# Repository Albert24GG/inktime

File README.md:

# InkTime Smartwatch

## Block Diagram

## Hardware Functionality

### Power Management
The power path starts at the **USB-C connector (5V)**, which feeds the **BQ25180 LiPo Charger**. This IC handles the 250mAh battery and provides a system rail (VSYS). To ensure a stable 3.3V regardless of the battery's state of charge, an **RT6160 Buck-Boost regulator** was used. This is critical because it keeps the MCU and E-paper display running even as the battery voltage drops. Furthermore, **MAX17048 Fuel Gauge** was included to get the battery percentage over I2C.

### Compute & Connectivity
The MCU chosen is **nRF52840**. It manages:
*   **I2C Bus:** Shared by the charger, regulator, fuel gauge, IMU, and haptic driver.
*   **SPI Bus:** Used exclusively for the E-paper display to handle fast screen refreshes.
*   **USB:** For firmware recovery and battery charging.
*   **RF:** A 2.4GHz trace leads to a chip antenna for BLE communication with a smartphone.

### Peripherals
*   **Display:** A 1.54" 200x200 E-paper module. Since these displays can leak power even when "off," we added a PFET-based power gate to completely cut VCC to the display during deep sleep.
*   **IMU:** The **BMA421** accelerometer handles step counting in hardware, waking the MCU only when a step is detected to save power.
*   **Haptics:** A **DRV2605L** driver controls an ERM shaker motor for haptic feedback.

## MCU Pinout Mapping

| Peripheral | Pin(s) | Function | Description |
| :--- | :--- | :--- | :--- |
| **I2C SDA** | P0.06 | Data | Shared bus for sensors and power ICs |
| **I2C SCL** | P0.07 | Clock | Shared bus for sensors and power ICs |
| **SPI SCK** | P0.02 | Clock | Dedicated high-speed SPI for E-Paper |
| **SPI MOSI** | P0.03 | Data Out | Dedicated high-speed SPI for E-Paper |
| **SPI CS** | P0.05 | Chip Sel | Dedicated high-speed SPI for E-Paper |
| **EPD DC** | P0.15 | Data/Cmd | Required for display command logic |
| **EPD RST** | P0.16 | Reset | Hardware reset for display controller |
| **EPD BUSY** | P0.17 | Input | MCU checks this before display updates |
| **EPD GATE** | P1.01 | PFET Ctrl | Cuts display power |
| **USB D+ / D-** | D+ / D- | USB Data | Differential pair for firmware/recovery |
| **VBUS** | VBUS | Detect | Used by MCU to detect USB cable attachment |
| **ANT1** | ANT | RF Out | 50-ohm matched trace to 2.4GHz chip antenna |
| **X1** | XC1 / XC2 | 32MHz | High-speed clock for Radio/System |
| **X2** | P0.00 / P0.01 | 32.768kHz | Low-power clock for RTC and Sleep timing |
| **IMU INT1** | P0.08 | Wake-up | Primary IMU interrupt |
| **IMU INT2** | P1.08 | Gesture | Secondary IMU interrupt for advanced gestures/events |
| **PMIC INT** | P0.11 | Charger | Signals charging status changes |
| **Fuel Alert** | P0.10 | Low Batt | Triggers when battery hits a critical % threshold |
| **Haptic EN** | P0.12 | Enable | Power control for the haptic driver |
| **Button Up** | P0.13 | Input | Navigation (Active Low) |
| **Button Dn** | P1.02 | Input | Navigation (Active Low) |
| **Button Ent** | P0.14 | Input | Enter / Confirm (Active Low) |
| **SWD Bus** | SWDIO/CLK | Debug | Programming via Tag-Connect TC2030 |
| **RESET** | P0.18 | Reset | System reset |
| **SWO** | P1.00 | Debug | SWO test pad |

## Design Log

During the development of the PCB and mechanical integration, several adjustments were made to ensure reliability and manufacturability:

*   **EPD Capacitor Tweak:** Changed **EPD_C5 to 1uF** (previously 100nF) after double-checking the display driver datasheet requirements for the internal charge pump.
*   **Silkscreen Optimization:** Because JLCPCB has a minimum text height of 1mm and our board is very dense, I removed labels for small passives. Only major components, connectors, and test pads have silkscreen labels to avoid a "messy" print.
*   **Bottom Layer Connectors:** The pads for the **Battery** and the **Shaker Motor** were moved to the **Bottom Layer**. Since these components live in the bottom of the case (under the PCB), this makes hand-soldering them much easier during assembly.
*   **Inner Layer Pad Cleanup:** To prevent manufacturing errors (shorts) with via-in-pad routing on the dense MCU footprint, I used the `Remove All Non-Functional Pads` option for the internal layers.
*   **Component Sizing:** While I aimed for 0201/0402 where possible, I used **0603 footprints** for the large inductors and decoupling caps in the DC/DC section to meet the voltage/current ratings.
*   **RF Optimization:** The antenna feedline (RF trace) was designed with a width of **0.1505mm**. This was calculated for a **50-ohm impedance match** based on the 4-layer stackup (Coplanar Waveguide with Ground).
*   **Accessibility:** All test pads were placed near the edges of the PCB so they can be reached easily with probes even when the display is mounted.
*   **GND & Thermal Management:** I applied a copper pour on the Top Layer with **via stitching** to the internal Ground Plane.
*   **Antenna Safety:** The antenna keepout zone follows the datasheet dimensions exactly. I also added **via fencing** around the keepout area to minimize interference with the rest of the components.
*   **Manufacturing Files**: CPL and BOM files are provided in JLCPCB standard format.

## Bill of Materials (BOM)

| Qty | Value | Parts | Device | Package | Description | Product Link | Datasheet Link |
|---|---|---|---|---|---|---|---|
| 17 | 1uF/50V | C15, C29, C30, C31, C32, C37, C38, EPD_C1, EPD_C2, EPD_C5, EPD_C6, EPD_C7, EPD_C8, EPD_C9, EPD_C10, EPD_C11, EPD_C12 | GRM155R61H105KE05D | 0402 | SMD Capacitor | [Link](https://jlcpcb.com/partdetail/1609005-GRM155R61H105KE05D/C1518208) | [Datasheet](https://wmsc.lcsc.com/wmsc/upload/file/pdf/v2/lcsc/2201180430_Murata-Electronics-GRM155R61H105KE05D_C1518208.pdf) |
| 6 | 4.7uF/25V | C6, C14, C20, C21, C43, C2-EP-DR | GRM155C61E475ME15D | 0402 | SMD Capacitor | [Link](https://jlcpcb.com/partdetail/6643118-GRM155C61E475ME15D/C5718966) | [Datasheet](https://wmsc.lcsc.com/wmsc/upload/file/pdf/v2/lcsc/2308111413_Murata-Electronics-GRM155C61E475ME15D_C5718966.pdf) |
| 2 | 10uF/25V | C1-EP-DR, C39 | GRM188R61E106KA73D | 0603 | SMD Capacitor | [Link](https://jlcpcb.com/partdetail/320824-GRM188R61E106KA73D/C344022) | [Datasheet](https://www.lcsc.com/datasheet/C344022.pdf) |
| 1 | 10uF/6.3V | C24 | GRM155R60J106ME44D | 0402 | SMD Capacitor | [Link](https://jlcpcb.com/partdetail/MurataElectronics-GRM155R60J106ME44D/C76991) | [Datasheet](https://wmsc.lcsc.com/wmsc/upload/file/pdf/v2/lcsc/2304140030_Murata-Electronics-GRM155R60J106ME44D_C76991.pdf) |
| 2 | 22uF/10V | C25, C33 | GRM188R61A226ME15D | 0603 | SMD Capacitor | [Link](https://jlcpcb.com/partdetail/MurataElectronics-GRM188R61A226ME15D/C84419) | [Datasheet](https://wmsc.lcsc.com/wmsc/upload/file/pdf/v2/lcsc/1810311140_Murata-Electronics-GRM188R61A226ME15D_C84419.pdf) |
| 9 | 100nF/25V | C5, C7, C8, C12, C19, C23, C27, C34, C42 | GRM033R61E104KE14D | 0201 | SMD Capacitor | [Link](https://jlcpcb.com/partdetail/MurataElectronics-GRM033R61E104KE14D/C76939) | [Datasheet](https://wmsc.lcsc.com/wmsc/upload/file/pdf/v2/lcsc/1811081532_Murata-Electronics-GRM033R61E104KE14D_C76939.pdf) |
| 1 | 100pF/50V | C11 | GRM0335C1H101JA01D | 0201 | SMD Capacitor | [Link](https://jlcpcb.com/partdetail/MurataElectronics-GRM0335C1H101JA01D/C76922) | [Datasheet](https://wmsc.lcsc.com/wmsc/upload/file/pdf/v2/lcsc/2304140030_Murata-Electronics-GRM0335C1H101JA01D_C76922.pdf) |
| 1 | 47nF/16V | C16 | GRM033R61C473KE84D | 0201 | SMD Capacitor | [Link](https://jlcpcb.com/partdetail/MurataElectronics-GRM033R61C473KE84D/C88917) | [Datasheet](https://wmsc.lcsc.com/wmsc/upload/file/pdf/v2/lcsc/2304140030_Murata-Electronics-GRM033R61C473KE84D_C88917.pdf) |
| 4 | 12pF/50V | C1, C2, C17, C18 | GRM0335C1H120FA01D | 0201 | SMD Capacitor | [Link](https://jlcpcb.com/partdetail/358666-GRM0335C1H120FA01D/C384960) | [Datasheet](https://www.lcsc.com/datasheet/C384960.pdf) |
| 2 | 1pf/50V | C3, C4 | GRM0335C1H1R0WA01D | 0201 | SMD Capacitor | [Link](https://jlcpcb.com/partdetail/172792-GRM0335C1H1R0WA01D/C161411) | [Datasheet](https://www.lcsc.com/datasheet/C161411.pdf) |
| 3 | 0Ω | R2, R3, R4 | RC0201FR-070RL | 0201 | SMD Resistor | [Link](https://jlcpcb.com/partdetail/YAGEO-RC0201FR070RL/C106227) | [Datasheet](https://www.lcsc.com/datasheet/C106227.pdf) |
| 1 | 470mΩ | R1_EP_DR | KDV02DR470ET | 0201 | SMD Resistor | [Link](https://jlcpcb.com/partdetail/Ohmite-KDV02DR470ET/C4327454) | [Datasheet](https://wmsc.lcsc.com/wmsc/upload/file/pdf/v2/lcsc/2404121342_Ohmite-KDV02DR470ET_C4327454.pdf) |
| 1 | 2.2Ω | R_TYPE_SEL | RC0201FR-072R2L | 0201 | SMD Resistor | [Link](https://jlcpcb.com/partdetail/YAGEO-RC0201FR072R2L/C138154) | [Datasheet](https://www.lcsc.com/datasheet/C138154.pdf) |
| 2 | 3.3KΩ | R17, R18 |  RC0201DR-073K3L| 0201 | SMD Resistor | [Link](https://jlcpcb.com/partdetail/YAGEO-RC0201DR073K3L/C851731) | [Datasheet](https://wmsc.lcsc.com/wmsc/upload/file/pdf/v2/lcsc/2206241815_YAGEO-RC0201DR-073K3L_C851731.pdf) |
| 2 |  5.1KΩ | R1_USB, R2_USB | RT0201BRD075K1L | 0201 | SMD Resistor | [Link](https://jlcpcb.com/partdetail/YAGEO-RT0201BRD075K1L/C852257) | [Datasheet](https://wmsc.lcsc.com/wmsc/upload/file/pdf/v2/lcsc/2210190401_YAGEO-RT0201BRD075K1L_C852257.pdf) |
| 6 | 10KΩ | R5, R7, R8, R9, R2_EP_DR, R_PWR_EPD | RE0201BRE0710KL | 0201 | SMD Resistor | [Link](https://jlcpcb.com/partdetail/YAGEO-RE0201BRE0710KL/C1882653) | [Datasheet](https://wmsc.lcsc.com/wmsc/upload/file/pdf/v2/lcsc/2201280400_YAGEO-RE0201BRE0710KL_C1882653.pdf) |
| 1 | 470nH | L7 | FTC252012SR47MBCA | 2520 | SMD Inductor | [Link](https://www.lcsc.com/product-detail/C5832368.html) | [Datasheet](https://www.lcsc.com/datasheet/C5832368.pdf) |
| 1 | 3.9nH | L1 | LQP03TN3N9B02D | 0201 | SMD Inductor | [Link](https://jlcpcb.com/partdetail/MurataElectronics-LQP03TN3N9B02D/C77115) | [Datasheet](https://wmsc.lcsc.com/wmsc/upload/file/pdf/v2/lcsc/2304140030_Murata-Electronics-LQP03TN3N9B02D_C77115.pdf) |
| 1 | 10uH | L2 | MLF1608E100JT000 | 0603 | SMD Inductor | [Link](https://jlcpcb.com/partdetail/TDK-MLF1608E100JT000/C275361) | [Datasheet](https://wmsc.lcsc.com/wmsc/upload/file/pdf/v2/lcsc/2304140030_TDK-MLF1608E100JT000_C275361.pdf) |
| 1 | 15nH | L3 | LQG15HS15NG02D | 0402 | SMD Inductor | [Link](https://jlcpcb.com/partdetail/MurataElectronics-LQG15HS15NG02D/C576527) | [Datasheet](https://wmsc.lcsc.com/wmsc/upload/file/pdf/v2/lcsc/2308111510_Murata-Electronics-LQG15HS15NG02D_C576527.pdf) |
| 1 | 68uH | L5 | 744043680 | SMD, 4.8x4.8mm | SMD Inductor | [Link](https://jlcpcb.com/partdetail/WurthElektronik-744043680/C2045671) | [Datasheet](https://www.we-online.com/components/products/datasheet/744043680.pdf) |
| 1 | USBLC6-2SC6Y | D3 | USBLC6-2SC6Y | SOT-23-6L | ESD Protection | [Link](https://jlcpcb.com/partdetail/STMicroelectronics-USBLC62SC6Y/C2969755) | [Datasheet](https://wmsc.lcsc.com/wmsc/upload/file/pdf/v2/lcsc/2211080730_STMicroelectronics-USBLC6-2SC6Y_C2969755.pdf) |
| 1 | KH-TYPE-C-16P | J4 | KH-TYPE-C-16P | SMD | USB Type-C Connector | [Link](https://jlcpcb.com/partdetail/Shenzhen_KinghelmElec-KH_TYPE_C16P/C709357) | [Datasheet](https://www.lcsc.com/datasheet/C709357.pdf) |
| 1 | 5034802400 | J1 | 5034802400 | SMD, P=0.5mm | Molex Display Connector | [Link](https://jlcpcb.com/partdetail/MOLEX-5034802400/C122434) | [Datasheet](https://www.molex.com/content/dam/molex/molex-dot-com/products/automated/en-us/salesdrawingpdf/503/503480/5034802400_sd.pdf) |
| 1 | MAX17048G+T10 | U3 | MAX17048G+T10 | DFN-8-EP(2x2) | Fuel Gauge | [Link](https://jlcpcb.com/partdetail/2777647-MAX17048GT10/C2682616) | [Datasheet](https://www.lcsc.com/datasheet/C2682616.pdf) |
| 3 | EVPAKE31A | SW_UP, SW_ENT, SW_DN | EVPAKE31A | SMD,3.9x2.9mm | Push Button | [Link](https://jlcpcb.com/partdetail/PANASONIC-EVPAKE31A/C569760) | [Datasheet](https://wmsc.lcsc.com/wmsc/upload/file/pdf/v2/lcsc/2301111010_PANASONIC-EVPAKE31A_C569760.pdf) |
| 1 | DRV2605YZFR | IC2 | DRV2605YZFR | DSBGA-9 | Haptic Driver | [Link](https://jlcpcb.com/partdetail/TexasInstruments-DRV2605YZFR/C81079) | [Datasheet](https://www.ti.com/cn/lit/ds/symlink/drv2605.pdf?ts=1775581743191&ref_url=https%253A%252F%252Fjlcpcb.com%252F) |
| 1 | DMG2305UX-7 | Q1 | DMG2305UX-7 | SOT-23 | EPD Power Gate | [Link](https://jlcpcb.com/partdetail/DiodesIncorporated-DMG2305UX7/C150470) | [Datasheet](https://www.lcsc.com/datasheet/C150470.pdf) |
| 1 | SI1308EDL-T1-GE3 | Q3 | SI1308EDL-T1-GE3 | SOT-323 | EPD Boost Converter Gate | [Link](https://jlcpcb.com/partdetail/VishayIntertech-SI1308EDL_T1GE3/C469327) | [Datasheet](https://www.lcsc.com/datasheet/C469327.pdf) |
| 3 | MBR0530 | D2, D4, D5 | MBR0530 | SOD-123 | EPD Boost Converter Schottky Diode | [Link](https://jlcpcb.com/partdetail/Yangzhou_Yangjie_ElecTech-MBR0530/C699108) | [Datasheet](https://www.lcsc.com/datasheet/C699108.pdf) |
| 1 | BMA421 | IC3 | BMA421 | LGA-12(2x2) | Accelerometer (IMU) | [Link](https://jlcpcb.com/partdetail/BoschSensortec-BMA421/C5242966) | [Datasheet](https://files.pine64.org/doc/datasheet/pinetime/BST-BMA421-FL000.pdf) |
| 1 | RT6160AWSC | IC9 | RT6160AWSC | WLCSP-15B(2.3x1.4) | DC/DC Converter | [Link](https://jlcpcb.com/partdetail/RichtekTech-RT6160AWSC/C7065276) | [Datasheet](https://wmsc.lcsc.com/wmsc/upload/file/pdf/v2/lcsc/2312271436_Richtek-Tech-RT6160AWSC_C7065276.pdf) |
| 1 | BQ25180YBGR | IC1 | BQ25180YBGR | DSBGA-8(1.1x1.6) | LiPo Charger | [Link](https://jlcpcb.com/partdetail/TexasInstruments-BQ25180YBGR/C3682423) | [Datasheet](https://www.ti.com/cn/lit/ds/symlink/bq25180.pdf?ts=1775521983580) |
| 1 | 2450AT18B100E | ANT1 | 2450AT18B100E | 1206 | RF Antenna | [Link](https://jlcpcb.com/partdetail/JohansonDielectrics-2450AT18B100E/C2917717) | [Datasheet](https://www.lcsc.com/datasheet/C2917717.pdf) |
| 1 | NRF52840-QIAA-R | U1 | NRF52840-QIAA-R | AQFN-73-EP(7x7) | Microcontroller (MCU) | [Link](https://jlcpcb.com/partdetail/NordicSemicon-NRF52840_QIAAR/C190794) | [Datasheet](https://www.lcsc.com/datasheet/C190794.pdf) |
| 1 | X1A0000910005 | X2 | X1A0000910005 | SMD3215-2P | Low Frequency Crystal | [Link](https://jlcpcb.com/partdetail/SeikoEpson-X1A0000910005/C255869) | [Datasheet](https://wmsc.lcsc.com/wmsc/upload/file/pdf/v2/lcsc/2008251105_Seiko-Epson-X1A0000910005_C255869.pdf) |
| 1 | Q22FA12800025 | X1 | Q22FA12800025 | SMD2016-4P | High Frequency Crystal | [Link](https://jlcpcb.com/partdetail/SeikoEpson-Q22FA12800025/C187794) | [Datasheet](https://www.lcsc.com/datasheet/C187794.pdf) |
| 1 | AKYGA LP502030 | - | AKYGA LP502030 | - | 3.7V/250mAh LiPo Battery | [Link](https://www.tme.eu/dk/en/details/aky-lp502030/rechargeable-batteries/akyga-battery/aky0106/) | [Datasheet](https://www.tme.eu/Document/b9e12bf26ad0ba929a22ab5d58f022cd/AKY0106.pdf) |
| 1 | WSH-12561 | - | WSH-12561 | - | 1.54" E-Paper Display, 200x200px | [Link](https://www.tme.eu/ie/en/details/wsh-12561/e-paper/waveshare/12561/) | [Datasheet](https://www.tme.eu/Document/0ca57a8ffbcd57b5bca53252eb9d6ec3/WSH-12561.pdf) |
| 1 | FIT0774 | - | FIT0774 | - | Shaker | [Link](https://www.tme.eu/ro/details/df-fit0774/motoare-dc/dfrobot/fit0774/) | [Datasheet](https://www.mouser.com/pdfDocs/ProductOverview_DFRobot-FIT0774.pdf) |
| 1 | TC2030-IDC | J2 | TC2030-IDC | PCB Footprint | Debug Connector | - | - |

## License
This project is licensed under the **MIT License**. See the `LICENSE` file for details.

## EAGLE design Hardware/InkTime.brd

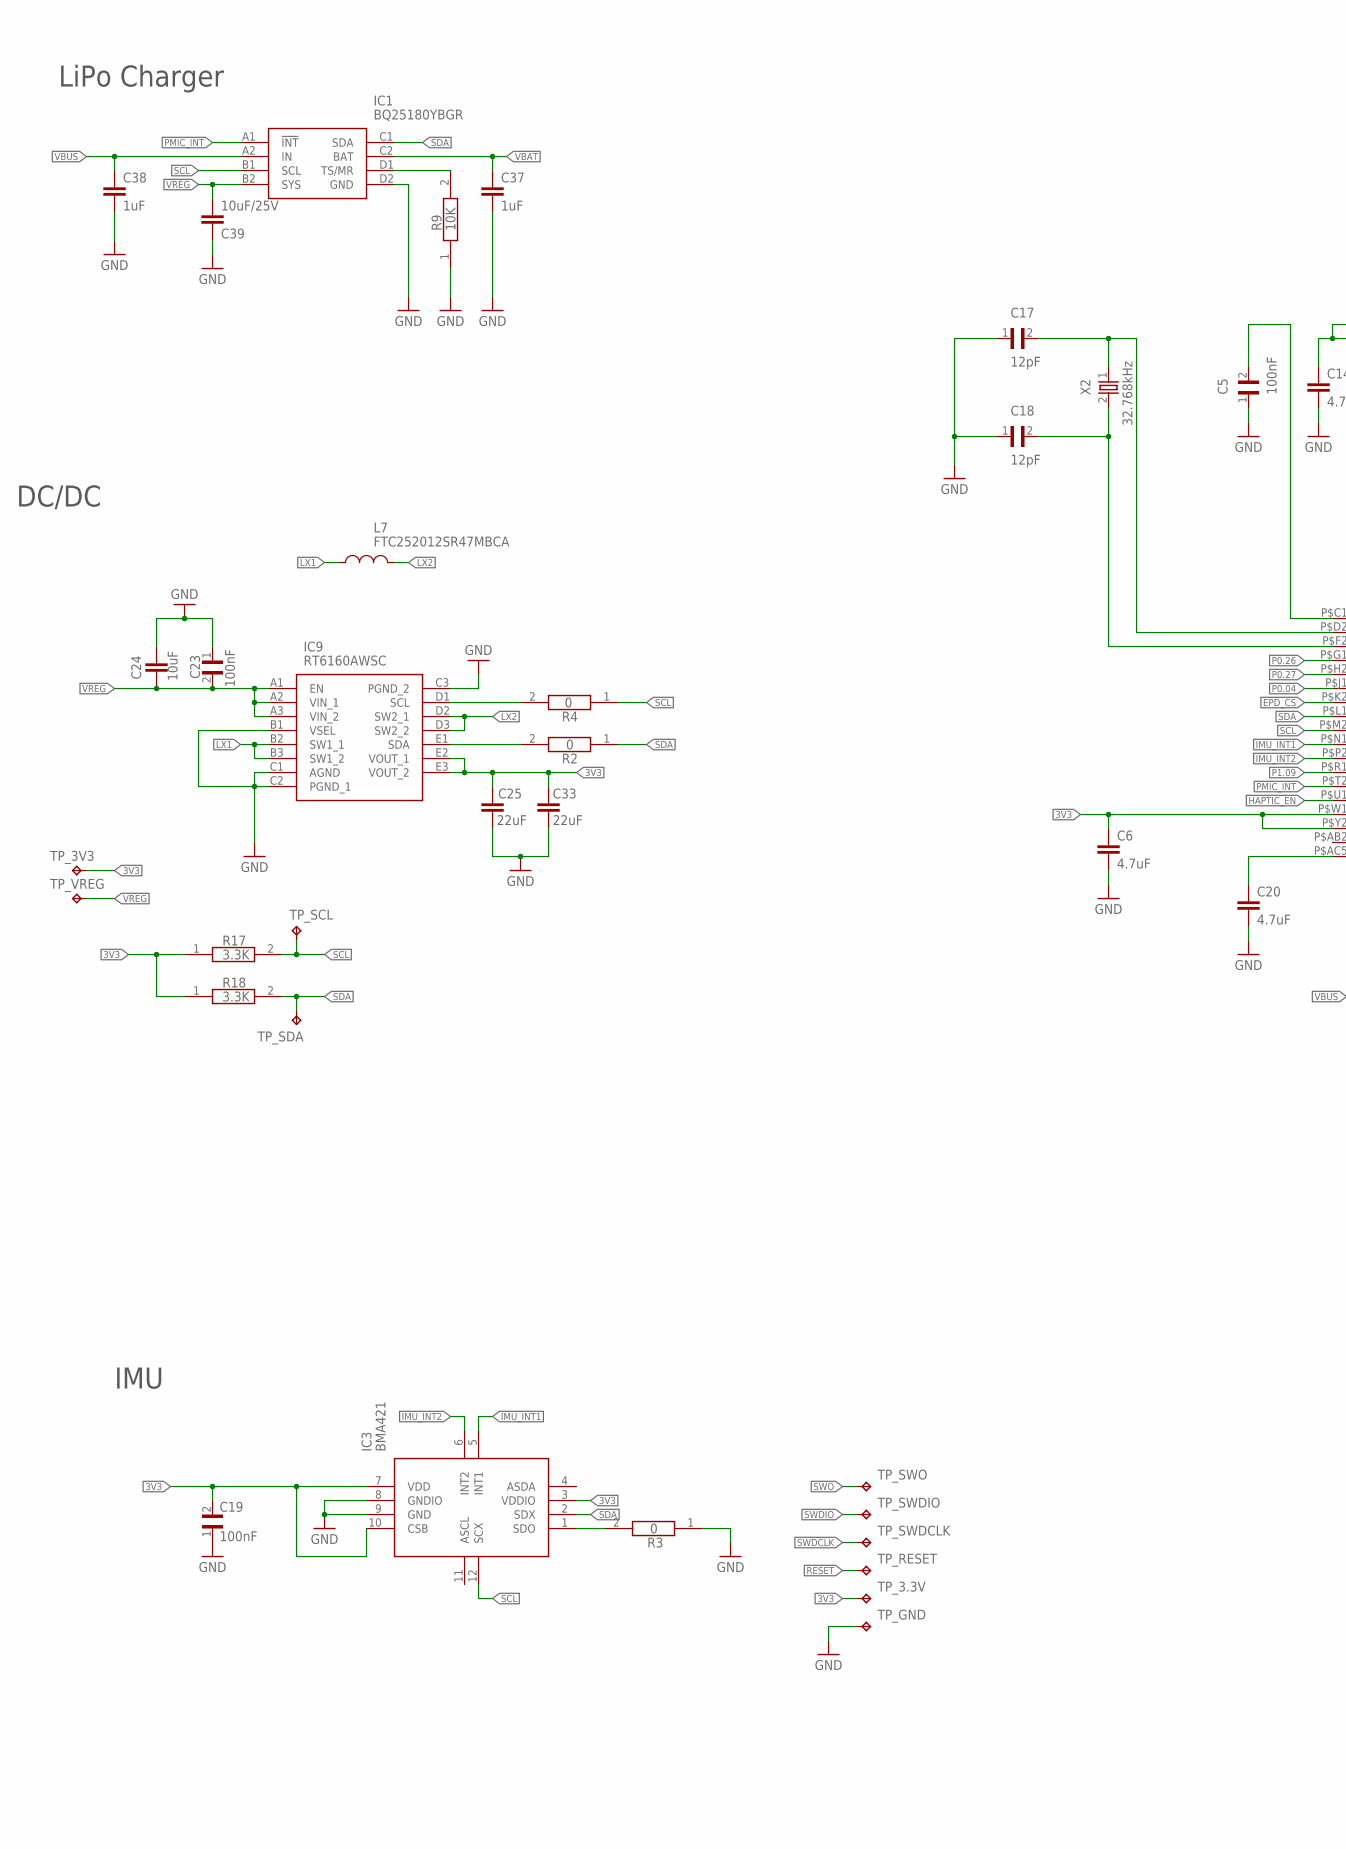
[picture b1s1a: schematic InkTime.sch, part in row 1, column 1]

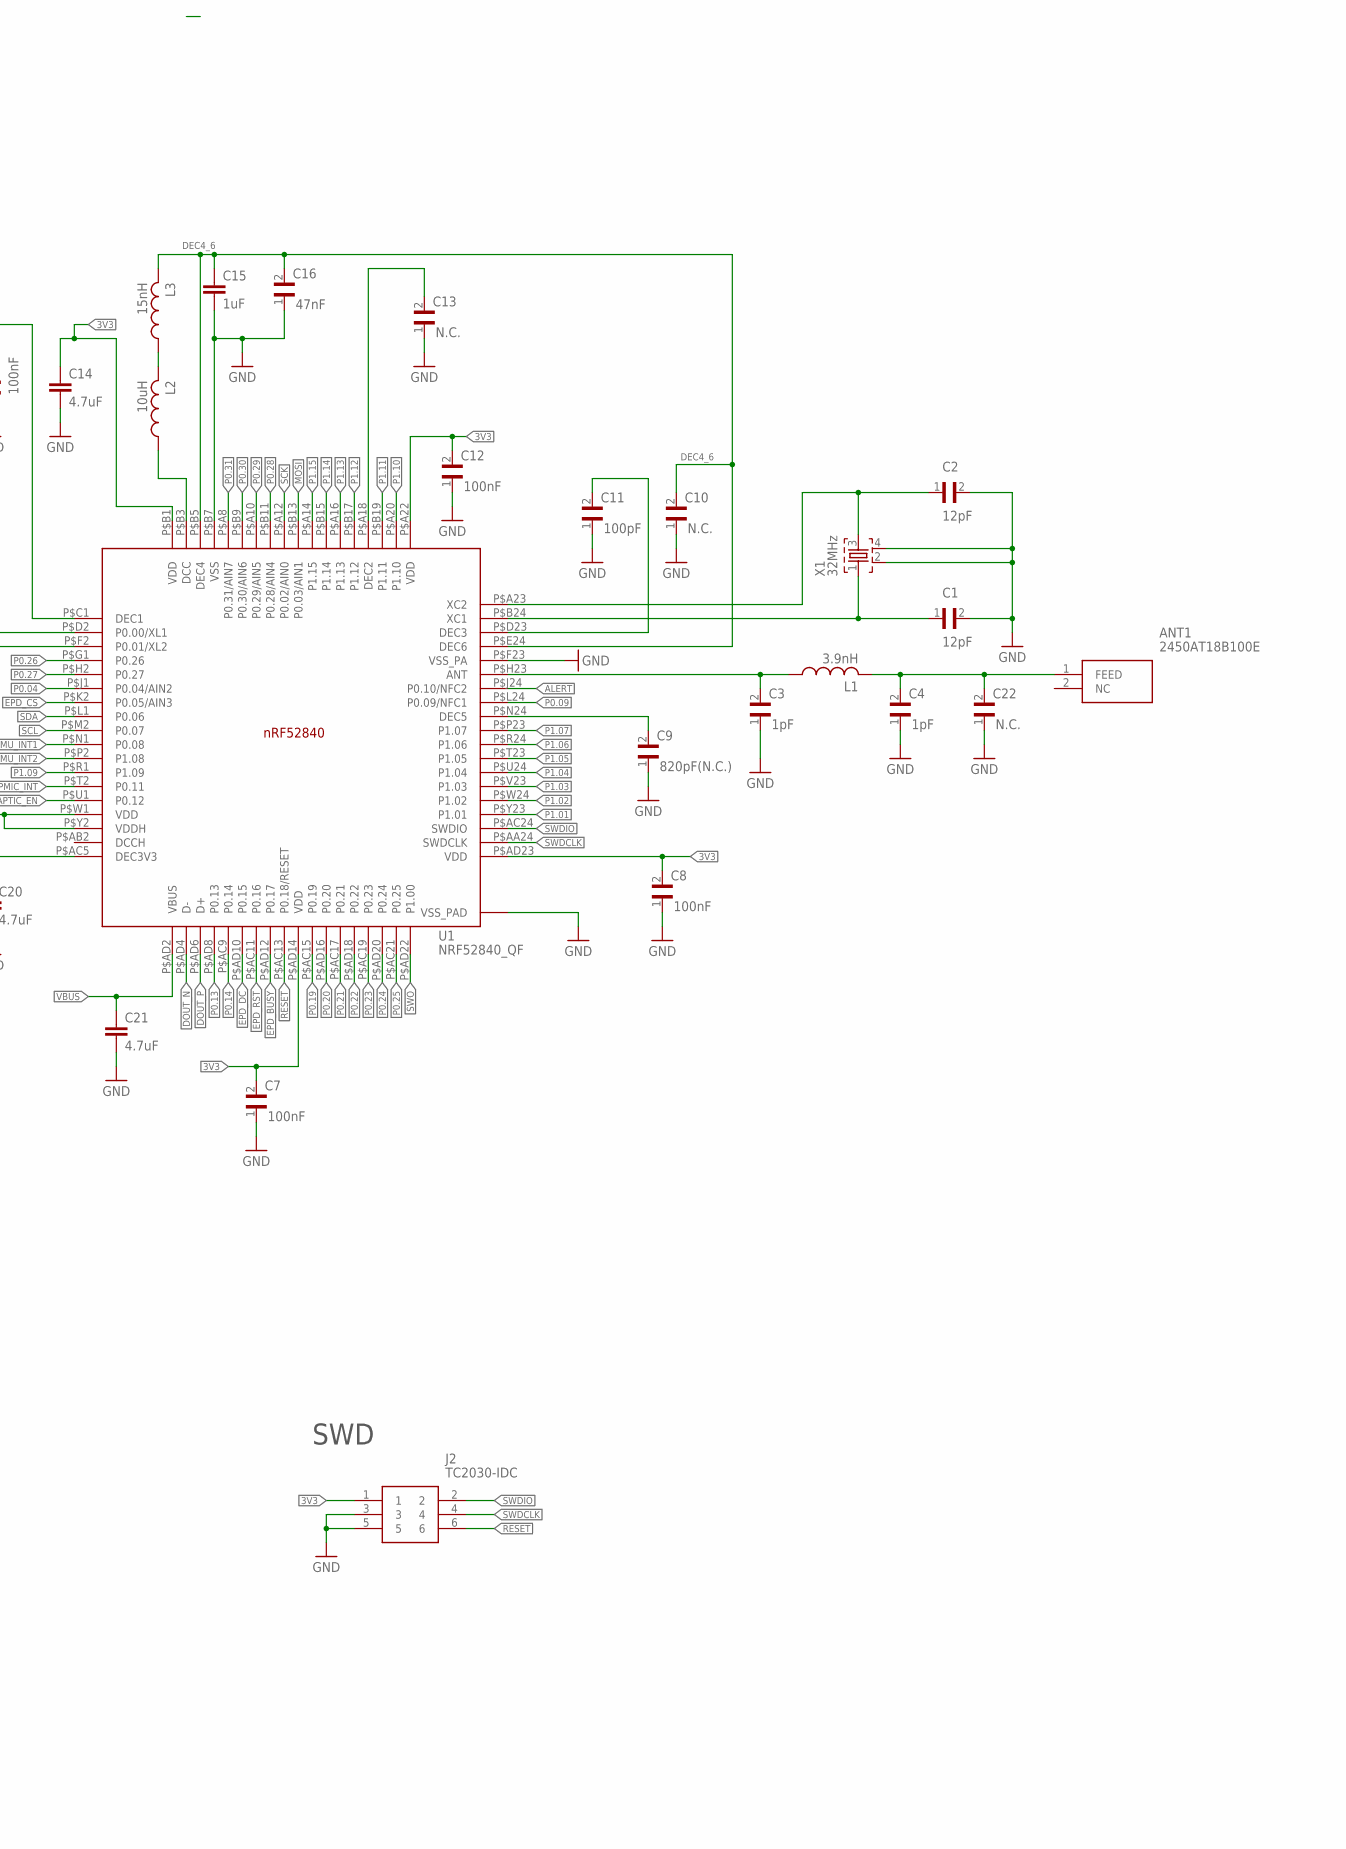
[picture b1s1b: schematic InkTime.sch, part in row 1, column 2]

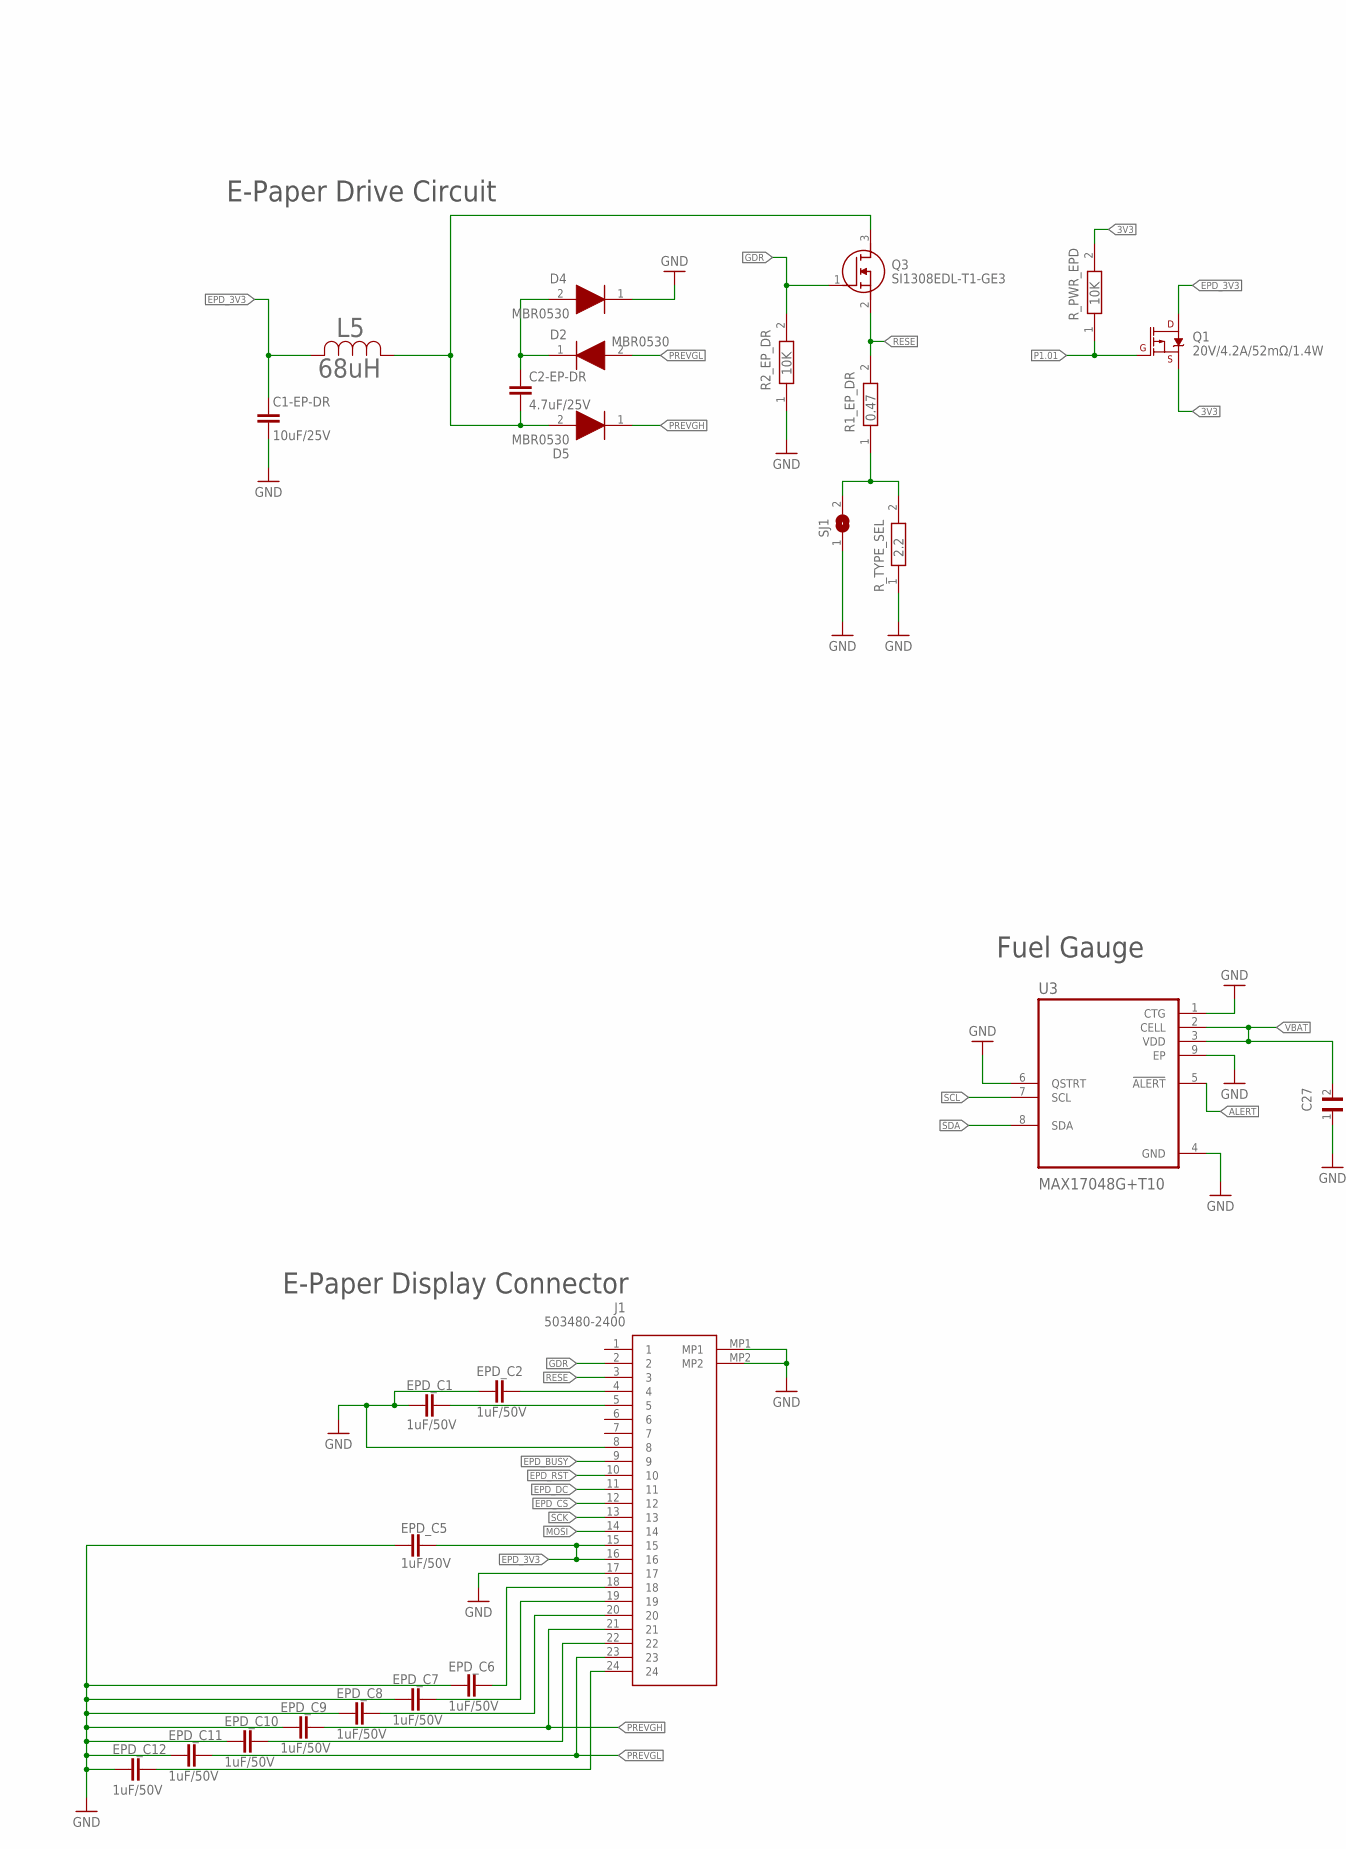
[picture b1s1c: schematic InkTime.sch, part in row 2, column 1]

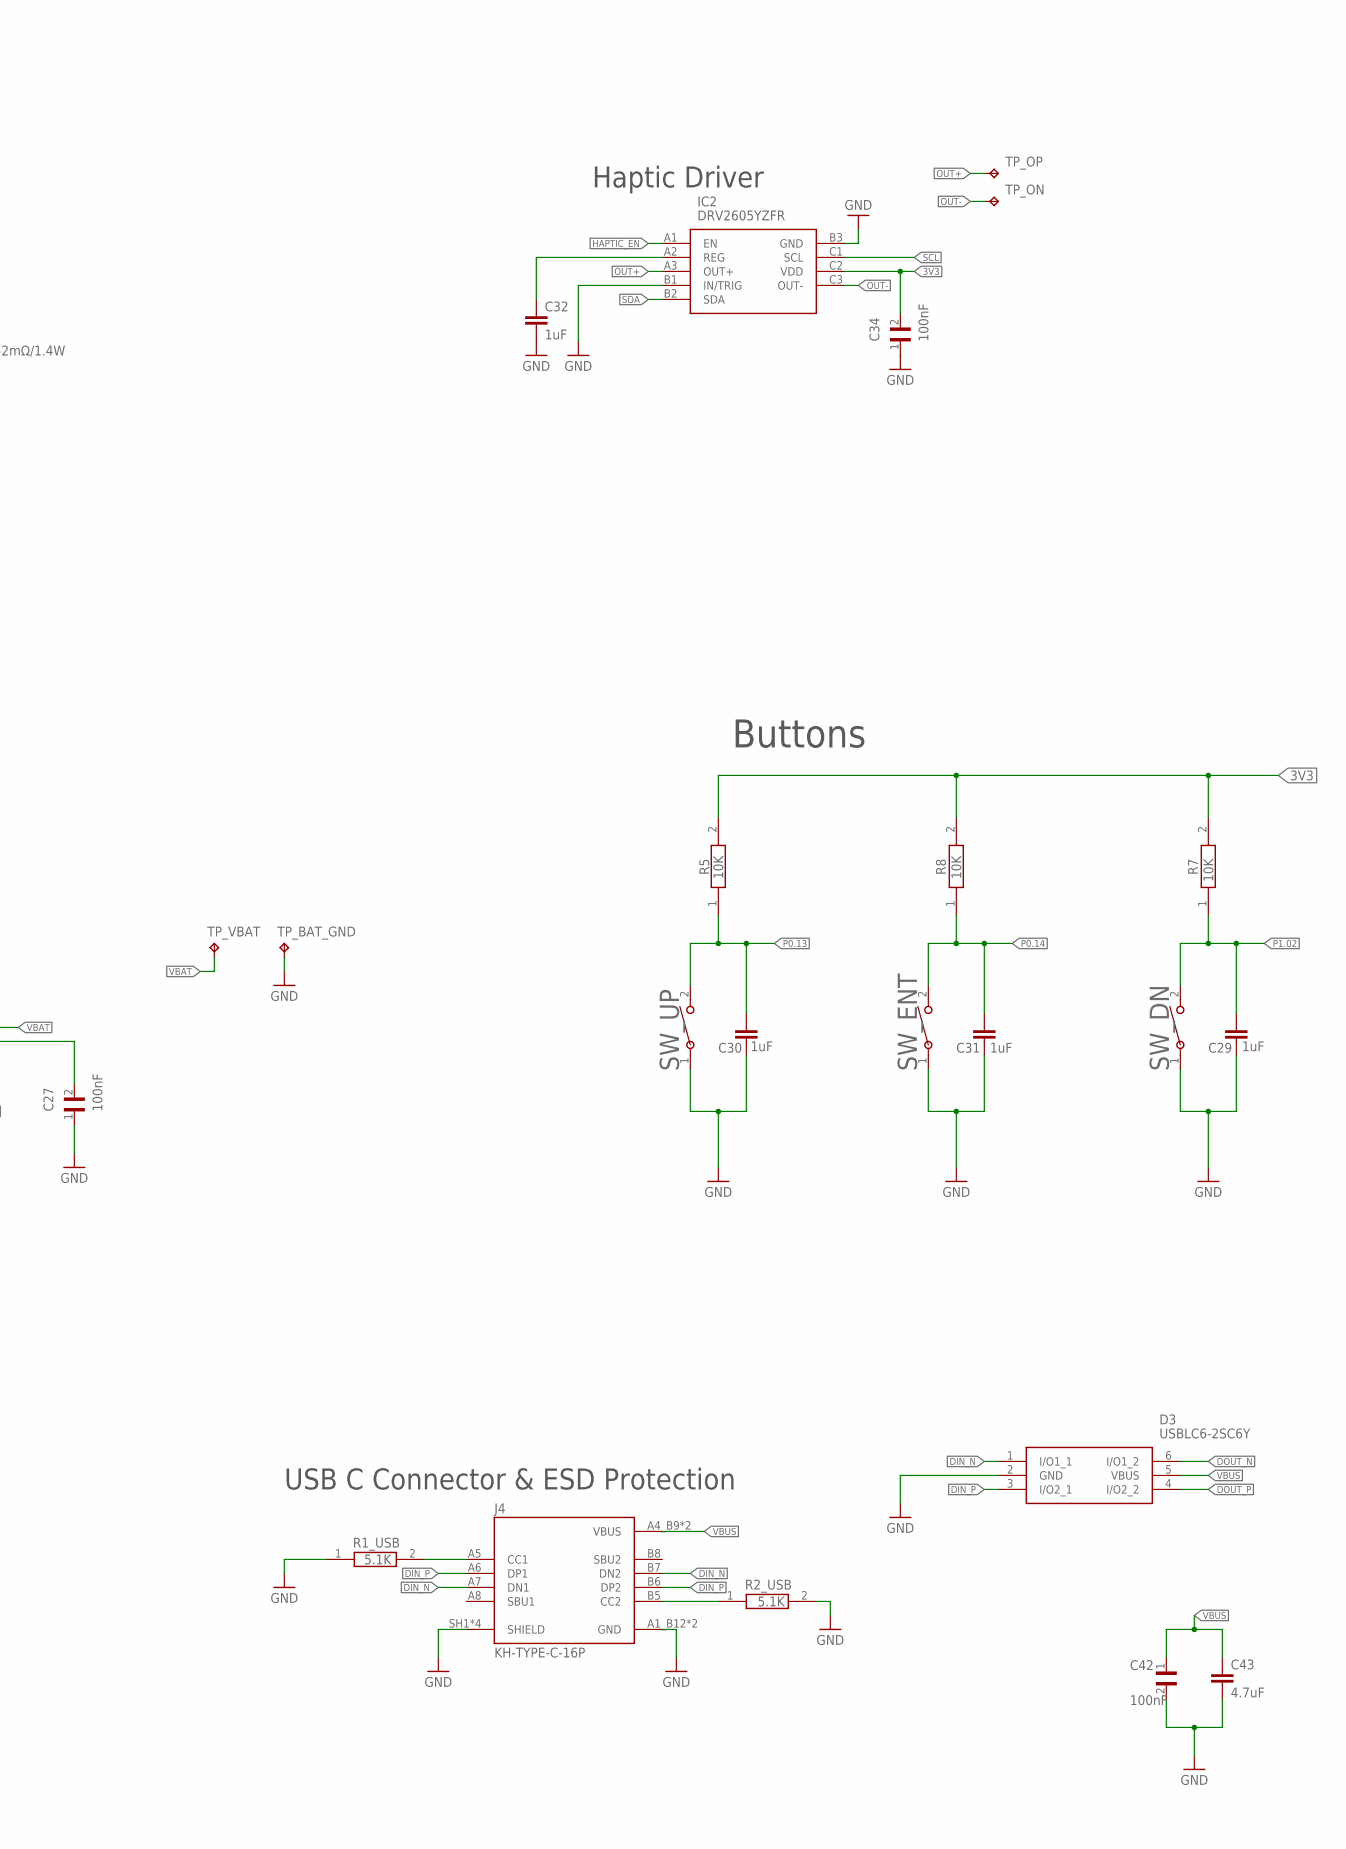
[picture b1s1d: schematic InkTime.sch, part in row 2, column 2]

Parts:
ANT1: 2450AT18B100E; 2450AT18B100E_ANTC3216X140N
C1, C2, C17, C18: 12pF; GRM011R60J152KE01L_2_CAPC0201X13N
C1-EP-DR, C39: 10uF/25V; NORDIC_NRF_3_RESC0603_N
C2-EP-DR: 4.7uF/25V; PERFECT_0402_0402
C3, C4: 1pF; GRM011R60J152KE01L_2_CAPC0201X13N
C5, C7, C8, C12, C19, C23, C27, C34, C42: 100nF; GRM011R60J152KE01L_2_CAPC0201X13N
C6, C14, C20, C21, C43: 4.7uF; PERFECT_0402_0402
C9: 820pF(N.C.); GRM011R60J152KE01L_2_CAPC0201X13N
C10, C13, C22: N.C.; GRM011R60J152KE01L_2_CAPC0201X13N
C11: 100pF; GRM011R60J152KE01L_2_CAPC0201X13N
C15, C29, C30, C31, C32, C37, C38: 1uF; PERFECT_0402_0402
C16: 47nF; GRM011R60J152KE01L_2_CAPC0201X13N
C24: 10uF; PERFECT_0402_0402
C25, C33: 22uF; NORDIC_NRF_3_RESC0603_N
D2, D4, D5: MBR0530; ESP32_C6_LIBRARY_5_SOD3716X135N
D3: USBLC6-2SC6Y; ESP32_C6_LIBRARY_3_SOT95P280X145-6N
EPD_C1, EPD_C2, EPD_C5, EPD_C6, EPD_C7, EPD_C8, EPD_C9, EPD_C10, EPD_C11, EPD_C12: 1uF/50V; PERFECT_0402_0402
IC1: BQ25180YBGR; BQ25180YBGR_BGA8C40P2X4_100X155X50
IC2: DRV2605YZFR; DRV2605YZFR_BGA9C50P3X3_144X144X62
IC3: BMA421; BMA423_BMA423
IC9: RT6160AWSC; RT6160AWSC_BGA15C40P3X5_140X230X60
J1: 503480-2400; 503480-2400_5034802400
J2: TC2030-IDC; TC2030-IDC_TC2030IDC
J4: KH-TYPE-C-16P; KH-TYPE-C-16P_KINGHELM_KH-TYPE-C-16P
L1: 3.9nH; NORDIC_NRF_2_RESC0201_N
L2: 10uH; NORDIC_NRF_2_RESC0603_N
L3: 15nH; NORDIC_NRF_2_RESC0402_N
L5: 68uH; ESP32_C6_LIBRARY_2_IND_4828-WE-TPC_WRE
L7: FTC252012SR47MBCA
Q1: 20V/4.2A/52mΩ/1.4W; ESP32_C6_LIBRARY_4_ESP32_C6_LIBRARY_4_ESP32_C6_LIBRARY_4_ES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
Q3: SI1308EDL-T1-GE3; ESP32_C6_LIBRARY_6_SOT65P210X110-3N
R1_EP_DR: 0.47; ERA-1AEB3401C_0201
R1_USB, R2_USB: 5.1K; ERA-1AEB3401C_0201
R2, R3, R4: 0; ERA-1AEB3401C_0201
R2_EP_DR, R5, R7, R8, R9: 10K; ERA-1AEB3401C_0201
R17, R18: 3.3K; ERA-1AEB3401C_0201
R_PWR_EPD: 10K; ERA-1AEB3401C_0201
R_TYPE_SEL: 2.2; ERA-1AEB3401C_0201
SJ1: ESP32_C6_LIBRARY_7_JUMPER_SJ
SW_DN: 2025-10-22_07-23-44_LIBRARY_EVP-AKE31ASW_EVP-AKE3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; 2025-10-22_07-23-44_LIBRARY_SW_EVP-AKE31A_PAN
SW_ENT: 2025-10-22_07-23-44_LIBRARY_EVP-AKE31ASW_EVP-AKE3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; 2025-10-22_07-23-44_LIBRARY_SW_EVP-AKE31A_PAN
SW_UP: 2025-10-22_07-23-44_LIBRARY_EVP-AKE31ASW_EVP-AKE3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; 2025-10-22_07-23-44_LIBRARY_SW_EVP-AKE31A_PAN
TP_3.3V, TP_3V3: HECTOR_WATCH_1_TPTP20R; HECTOR_WATCH_1_TP20R
TP_BAT_GND: HECTOR_WATCH_1_TPTP20R; HECTOR_WATCH_1_TP20R
TP_GND: HECTOR_WATCH_1_TPTP20R; HECTOR_WATCH_1_TP20R
TP_ON: HECTOR_WATCH_1_TPTP20R; HECTOR_WATCH_1_TP20R
TP_OP: HECTOR_WATCH_1_TPTP20R; HECTOR_WATCH_1_TP20R
TP_RESET: HECTOR_WATCH_1_TPTP20R; HECTOR_WATCH_1_TP20R
TP_SCL: HECTOR_WATCH_1_TPTP20R; HECTOR_WATCH_1_TP20R
TP_SDA: HECTOR_WATCH_1_TPTP20R; HECTOR_WATCH_1_TP20R
TP_SWDCLK: HECTOR_WATCH_1_TPTP20R; HECTOR_WATCH_1_TP20R
TP_SWDIO: HECTOR_WATCH_1_TPTP20R; HECTOR_WATCH_1_TP20R
TP_SWO: HECTOR_WATCH_1_TPTP20R; HECTOR_WATCH_1_TP20R
TP_VBAT: HECTOR_WATCH_1_TPTP20R; HECTOR_WATCH_1_TP20R
TP_VREG: HECTOR_WATCH_1_TPTP20R; HECTOR_WATCH_1_TP20R
U1: NRF52840_QF; NORDIC_NRF_4_AQFN50P700X700X85_HS-74N
U3: MAX17048G+T10; ESP32_C6_LIBRARY_SON50P200X200X80-9N
X1: 32MHz; NORDIC_NRF_BT-XTAL_2016_N
X2: 32.768kHz; NORDIC_NRF_1_XTAL_3215_N

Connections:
3V3: C6.1, C7.2, C8.2, C12.2, C14.1, C19.2, C25.1, C33.1, C34.2, IC2.C2 (VDD), IC3.3 (VDDIO), IC3.7 (VDD), IC3.10 (CSB), IC9.E2 (VOUT_1), IC9.E3 (VOUT_2), J2.1, Q1.2 (S), R5.2, R7.2, R8.2, R17.1, R18.1, R_PWR_EPD.2, TP_3.3V.TP, TP_3V3.TP, U1.P$A22 (VDD), U1.P$AD14 (VDD), U1.P$AD23 (VDD), U1.P$B1 (VDD), U1.P$W1 (VDD), U1.P$Y2 (VDDH)
ALERT: U1.P$J24 (P0.10/NFC2), U3.5 (!ALERT)
DEC4_6: C10.2, C15.1, C16.2, L3.2, U1.P$B5 (DEC4), U1.P$E24 (DEC6)
DIN_N: D3.1 (I/O1_1), J4.A7 (DN1), J4.B7 (DN2)
DIN_P: D3.3 (I/O2_1), J4.A6 (DP1), J4.B6 (DP2)
DOUT_N: D3.6 (I/O1_2), U1.P$AD4 (D-)
DOUT_P: D3.4 (I/O2_2), U1.P$AD6 (D+)
EPD_3V3: C1-EP-DR.1, EPD_C5.2, J1.15, J1.16, L5.2, Q1.3 (D)
EPD_BUSY: J1.9, U1.P$AD12 (P0.17)
EPD_CS: J1.12, U1.P$K2 (P0.05/AIN3)
EPD_DC: J1.11, U1.P$AD10 (P0.15)
EPD_RST: J1.10, U1.P$AC11 (P0.16)
GDR: J1.2, Q3.1 (G), R2_EP_DR.2
GND: C1.2, C1-EP-DR.2, C2.2, C3.1, C4.1, C5.1, C6.2, C7.1, C8.1, C9.1, C10.1, C11.1, C12.1, C13.1, C14.2, C15.2, C16.1, C17.1, C18.1, C19.1, C20.2, C21.2, C22.1, C23.1, C24.1, C25.2, C27.1, C29.1, C30.1, C31.1, C32.2, C33.2, C34.1, C37.2, C38.2, C39.2, C42.2, C43.2, D3.2 (GND), D4.1 (K), EPD_C1.1, EPD_C2.1, EPD_C5.1, EPD_C6.1, EPD_C7.1, EPD_C8.1, EPD_C9.1, EPD_C10.1, EPD_C11.1, EPD_C12.1, IC1.D2 (GND), IC2.B1 (IN/TRIG), IC2.B3 (GND), IC3.8 (GNDIO), IC3.9 (GND), IC9.B1 (VSEL), IC9.C1 (AGND), IC9.C2 (PGND_1), IC9.C3 (PGND_2), J1.8, J1.17, J1.MP1, J1.MP2, J2.3, J2.5, J4.A1_B12 (GND), J4.A12_B1 (GND), J4.SH1 (SHIELD), J4.SH2 (SHIELD), J4.SH3 (SHIELD), J4.SH4 (SHIELD), R1_USB.1, R2_EP_DR.1, R2_USB.2, R3.1, R9.1, R_TYPE_SEL.1, SJ1.1, SW_DN.1, SW_ENT.1, SW_UP.1, TP_BAT_GND.TP, TP_GND.TP, U1.P$74 (VSS_PAD), U1.P$75 (VSS_PAD), U1.P$76 (VSS_PAD), U1.P$77 (VSS_PAD), U1.P$78 (VSS_PAD), U1.P$79 (VSS_PAD), U1.P$80 (VSS_PAD), U1.P$81 (VSS_PAD), U1.P$82 (VSS_PAD), U1.P$83 (VSS_PAD), U1.P$84 (VSS_PAD), U1.P$85 (VSS_PAD), U1.P$86 (VSS_PAD), U1.P$87 (VSS_PAD), U1.P$88 (VSS_PAD), U1.P$89 (VSS_PAD), U1.P$90 (VSS_PAD), U1.P$B7 (VSS), U1.P$F23 (VSS_PA), U3.1 (CTG), U3.4 (GND), U3.6 (QSTRT), U3.9 (EP), X1.2, X1.4
HAPTIC_EN: IC2.A1 (EN), U1.P$U1 (P0.12)
IMU_INT1: IC3.5 (INT1), U1.P$N1 (P0.08)
IMU_INT2: IC3.6 (INT2), U1.P$P2 (P1.08)
LX1: IC9.B2 (SW1_1), IC9.B3 (SW1_2), L7.1
LX2: IC9.D2 (SW2_1), IC9.D3 (SW2_2), L7.2
MOSI: J1.14, U1.P$B13 (P0.03/AIN1)
unnamed: J4.A5 (CC1), R1_USB.2
unnamed: EPD_C12.2, J1.24
unnamed: C17.2, U1.P$D2 (P0.00/XL1), X2.1
unnamed: EPD_C2.2, J1.4
unnamed: C20.1, U1.P$AC5 (DEC3V3)
unnamed: EPD_C1.2, J1.5
unnamed: EPD_C10.2, J1.22
unnamed: J4.B5 (CC2), R2_USB.1
unnamed: C32.1, IC2.A2 (REG)
unnamed: EPD_C8.2, J1.20
unnamed: EPD_C7.2, J1.19
unnamed: EPD_C6.2, J1.18
unnamed: C2-EP-DR.2, D5.2 (A), L5.1, Q3.3 (D)
unnamed: C2-EP-DR.1, D2.1 (K), D4.2 (A)
unnamed: IC9.D1 (SCL), R4.2
unnamed: C18.2, U1.P$F2 (P0.01/XL2), X2.2
unnamed: C5.2, U1.P$C1 (DEC1)
unnamed: R1_EP_DR.1, R_TYPE_SEL.2, SJ1.2
unnamed: IC3.1 (SDO), R3.2
unnamed: IC9.E1 (SDA), R2.2
unnamed: L2.2, L3.1
unnamed: C2.1, U1.P$A23 (XC2), X1.3
unnamed: IC1.D1 (TS/MR), R9.2
unnamed: C13.2, U1.P$A18 (DEC2)
unnamed: L2.1, U1.P$B3 (DCC)
unnamed: C11.2, U1.P$D23 (DEC3)
unnamed: C1.1, U1.P$B24 (XC1), X1.1
unnamed: C9.2, U1.P$N24 (DEC5)
unnamed: C3.2, L1.1, U1.P$H23 (ANT)
unnamed: ANT1.1 (FEED), C4.2, C22.2, L1.2
OUT+: IC2.A3 (OUT+), TP_OP.TP
OUT-: IC2.C3 (OUT-), TP_ON.TP
P0.04: U1.P$J1 (P0.04/AIN2)
P0.09: U1.P$L24 (P0.09/NFC1)
P0.13: C30.2, R5.1, SW_UP.2, U1.P$AD8 (P0.13)
P0.14: C31.2, R8.1, SW_ENT.2, U1.P$AC9 (P0.14)
P0.19: U1.P$AC15 (P0.19)
P0.20: U1.P$AD16 (P0.20)
P0.21: U1.P$AC17 (P0.21)
P0.22: U1.P$AD18 (P0.22)
P0.23: U1.P$AC19 (P0.23)
P0.24: U1.P$AD20 (P0.24)
P0.25: U1.P$AC21 (P0.25)
P0.26: U1.P$G1 (P0.26)
P0.27: U1.P$H2 (P0.27)
P0.28: U1.P$B11 (P0.28/AIN4)
P0.29: U1.P$A10 (P0.29/AIN5)
P0.30: U1.P$B9 (P0.30/AIN6)
P0.31: U1.P$A8 (P0.31/AIN7)
P1.01: Q1.1 (G), R_PWR_EPD.1, U1.P$Y23 (P1.01)
P1.02: C29.2, R7.1, SW_DN.2, U1.P$W24 (P1.02)
P1.03: U1.P$V23 (P1.03)
P1.04: U1.P$U24 (P1.04)
P1.05: U1.P$T23 (P1.05)
P1.06: U1.P$R24 (P1.06)
P1.07: U1.P$P23 (P1.07)
P1.09: U1.P$R1 (P1.09)
P1.10: U1.P$A20 (P1.10)
P1.11: U1.P$B19 (P1.11)
P1.12: U1.P$B17 (P1.12)
P1.13: U1.P$A16 (P1.13)
P1.14: U1.P$B15 (P1.14)
P1.15: U1.P$A14 (P1.15)
PMIC_INT: IC1.A1 (!INT), U1.P$T2 (P0.11)
PREVGH: D5.1 (K), EPD_C9.2, J1.21
PREVGL: D2.2 (A), EPD_C11.2, J1.23
RESE: J1.3, Q3.2 (S), R1_EP_DR.2
RESET: J2.6, TP_RESET.TP, U1.P$AC13 (P0.18/RESET)
SCK: J1.13, U1.P$A12 (P0.02/AIN0)
SCL: IC1.B1 (SCL), IC2.C1 (SCL), IC3.12 (SCX), R4.1, R17.2, TP_SCL.TP, U1.P$M2 (P0.07), U3.7 (SCL)
SDA: IC1.C1 (SDA), IC2.B2 (SDA), IC3.2 (SDX), R2.1, R18.2, TP_SDA.TP, U1.P$L1 (P0.06), U3.8 (SDA)
SWDCLK: J2.4, TP_SWDCLK.TP, U1.P$AA24 (SWDCLK)
SWDIO: J2.2, TP_SWDIO.TP, U1.P$AC24 (SWDIO)
SWO: TP_SWO.TP, U1.P$AD22 (P1.00)
VBAT: C27.2, C37.1, IC1.C2 (BAT), TP_VBAT.TP, U3.2 (CELL), U3.3 (VDD)
VBUS: C21.1, C38.1, C42.1, C43.1, D3.5 (VBUS), IC1.A2 (IN), J4.A4_B9 (VBUS), J4.A9_B4 (VBUS), U1.P$AD2 (VBUS)
VREG: C23.2, C24.2, C39.1, IC1.B2 (SYS), IC9.A1 (EN), IC9.A2 (VIN_1), IC9.A3 (VIN_2), TP_VREG.TP

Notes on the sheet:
Buttons
USB C Connector & ESD Protection
Fuel Gauge
E-Paper Display Connector
Haptic Driver
E-Paper Drive Circuit
IMU
SWD
DC/DC
LiPo Charger

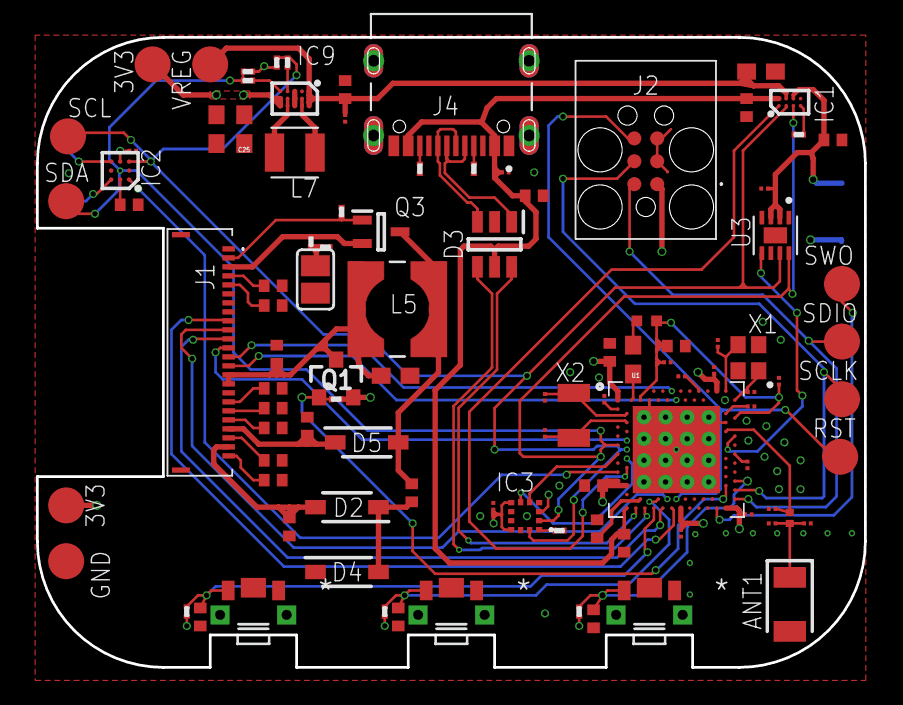
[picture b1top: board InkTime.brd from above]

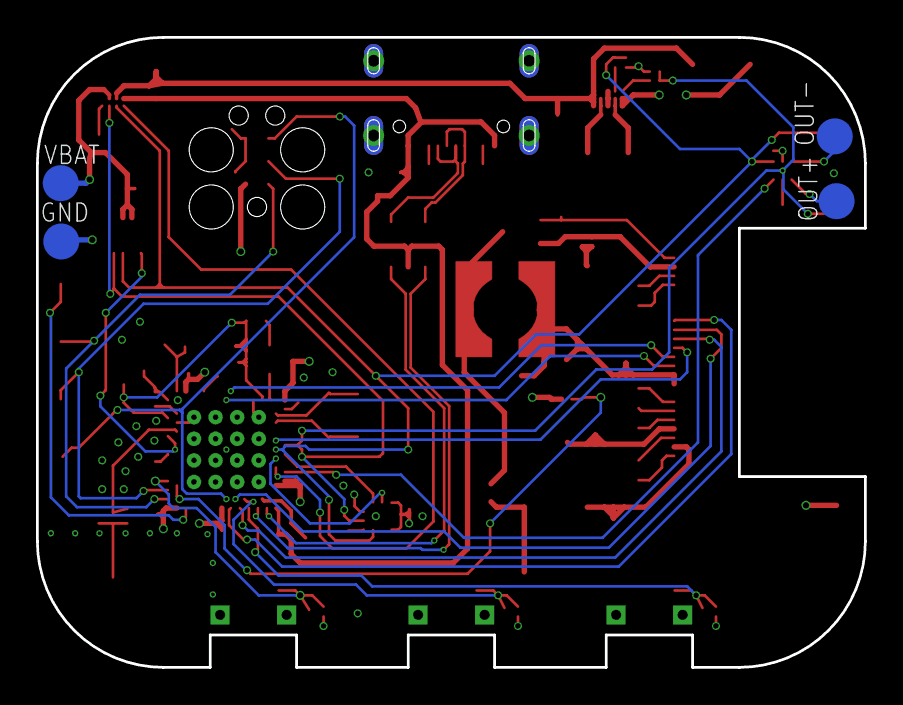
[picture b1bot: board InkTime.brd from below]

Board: 4 copper layers, 46.0 x 35.0 mm, 105 parts (4 on the bottom side), 70 nets.

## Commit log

2026-04-10 Add exploded 3d model
2026-04-11 Update cpl and bom
2026-04-11 Clear via-in-pad erros
2026-04-11 Add renderings
2026-04-17 Update pinout table
2026-04-17 Fix battery/bottomcase and display/topcase overlap
2026-04-17 Add frame to schematic
2026-04-17 Replace .brd/.sch with .fbrd/.fsch
2026-04-19 Remove stray wire from schematic
2026-04-19 Fix text placement in schematic
2026-04-19 Add schematic print-out
2026-04-20 Use the correct library component for the 0201/0402 capacitors

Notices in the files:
parts and their libraries:
COPYRIGHT: Copyright (C) 2024 Ultra Librarian. All rights reserved.
COPYRIGHT: Copyright (C) 2025 Ultra Librarian. All rights reserved.
